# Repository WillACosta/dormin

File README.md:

## Dormin Split Keyboard

> 3×6 (+2 outer-pinky) Split Keyboard · 3 Thumb Keys · All 1U · MX Compatible

Dormin is a 42 — 36 keys split keyboard, inspired by some awesome keyboards that I've used and loved. The main goal is to create a customizable keyboard with optional features, but still as minimal as possible regarding the design.

### Must have specs

- Wireless Ble.
- Ultra low-profile build (<= 7mm).
- Low-profile switches and keycaps.
- Compatible with MX-Standard and the Gateron KS33/3.0 Low-Profile switches & Choc V2.
- Huge battery life (1200mAh).
- Minimalist and industrial design.
- Aluminum case and plate.
- 4 different layouts trough breakaway parts.
- Split and "Unibody" layouts (Using Pogo pins)
- MX-Spacing
- Status LEDs

**Optional**

- EC12 Rotatory Encoder
- SD OLED screen or Nice!View

## Layout Overview

The Dormin is a **40-key split keyboard** (20 keys per half) with a column-staggered matrix and a splayed thumb cluster.

| Zone | Columns | Rows | Keys/half | Notes |
|------|---------|------|-----------|-------|
| Matrix | 6 (outer → inner) | 3 (bottom, home, top) | 17 | Outer column skips bottom row (2 keys only) |
| Thumb | 3 (inner, home, outer) | 1 | 3 | Splayed arc, anchored below index |
| **Total** | | | **20** | **40 keys full board** |

### Column Stagger Profile

```
         outer  pinky  ring   middle  index  inner
stagger:   —    +u/2   +u/4   +u/4   −u/4   −u/4
mm:        0    +9.525 +4.763 +4.763 −4.763 −4.763
```

```
                    ┌──┐┌──┐
               ┌──┐ │  ││  │ ┌──┐
          ┌──┐ │  │ │Mi││Mi│ │  │ ┌──┐
     ┌──┐ │  │ │Ri││dd││dd│ │In│ │  │
     │  │ │Pi│ │ng││le││le│ │ne│ │  │
     │Ou│ │nk│ │  ││  ││  │ │r │ │  │
     │te│ │y │ │  ││  ││  │ │  │ │  │
     │r │ │  │ │  ││  ││  │ │  │ │  │
     └──┘ │  │ │  │└──┘└──┘ │  │ │  │
          └──┘ └──┘          └──┘ └──┘
                    ┌──┐
               ┌──┐│  │┌──┐
               │Th ││Th││Th│
               │ 3 ││ 2││ 1│
               └──┘└──┘└──┘
```

### Thumb Cluster Geometry

| Key | Splay | Spread | Stagger | Effective rotation |
|-----|-------|--------|---------|--------------------|
| thumb_inner | 0° | u (19.05mm) | 0mm | 0° |
| thumb_home | −15° | u+2.5 (21.55mm) | −2.7mm | −15° |
| thumb_outer | −14° | u+2.5 (21.55mm) | −2.5mm | −29° |

The thumb cluster anchors at `matrix_index_bottom` with a `[-0.1u, -1.30u]` offset, placing it slightly left and well below the index column — a natural resting position for the thumb.

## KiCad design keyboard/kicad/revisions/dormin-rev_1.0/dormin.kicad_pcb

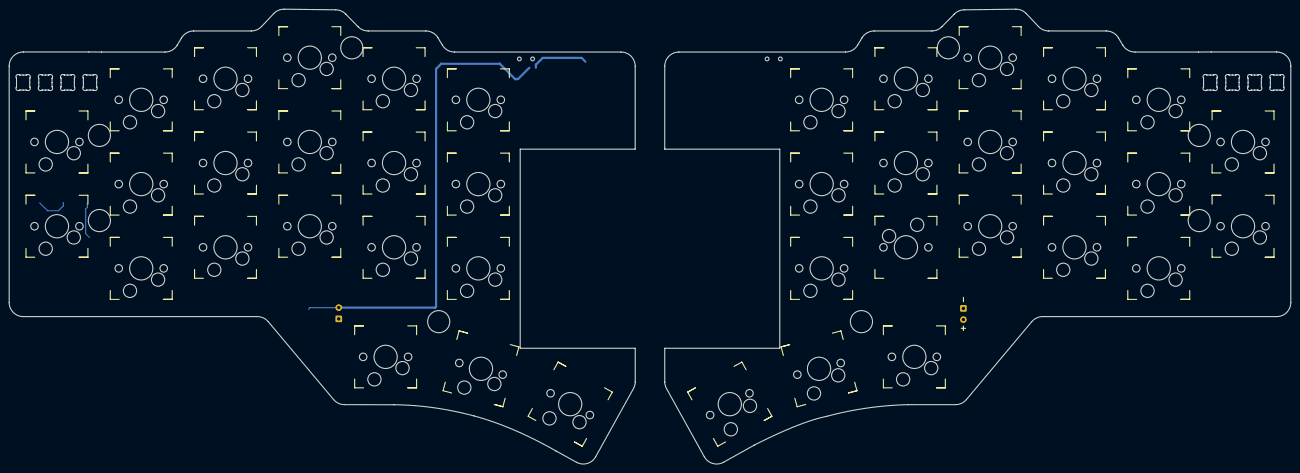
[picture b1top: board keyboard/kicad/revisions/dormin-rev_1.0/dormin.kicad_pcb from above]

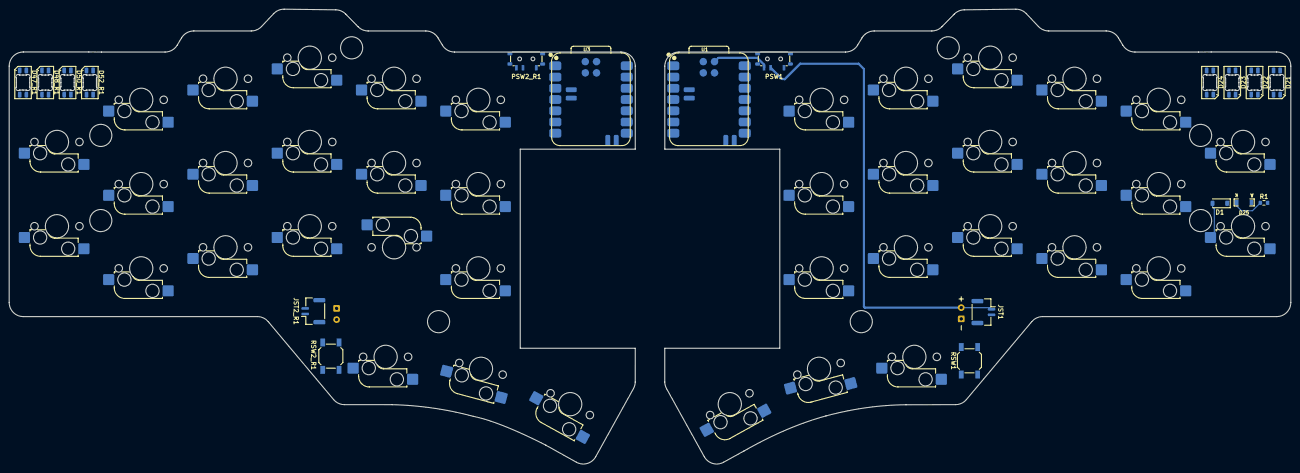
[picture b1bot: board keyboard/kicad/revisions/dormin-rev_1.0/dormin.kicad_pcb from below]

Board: 2 copper layers, 289.7 x 102.8 mm, 61 parts (20 on the bottom side), 31 nets.

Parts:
BT1, BT2_R1: Pads; Battery_Pad
D1: 1N4148W; D_SOD-123
D21, D22, D23, D24, D47_R1, D48_R1, D50_R1, D52_R1: SK6812MINI-E; LED_SK6812MINI-E_3.2x2.8mm_P1.5mm_ReverseMount
D25: LED; LED_MHT151WDT
JST1, JST2_R1: Conn_01x02_Pin; JST_GH_SM02B-GHS-TB_1x02-1MP_P1.25mm_Horizontal
PSW1, PSW2_R1: SW_SPDT; SW_MSK12C02-HB
R1: 1K; R_0603_1608Metric
RSW1, RSW2_R1: RSW1; SW_SPST_SKQG_WithStem
SW1, SW2, SW3, SW4, SW5, SW6, SW7, SW8, SW9, SW10, SW11, SW12, SW13, SW14, SW15, SW16, SW17, SW18, SW19, SW20, SW21, SW22, SW23, SW24, SW25, SW26, SW27, SW28, SW29, SW30, SW31, SW32, SW33, SW34, SW35, SW36, SW37, SW38, SW39, SW40: SW_Push; NF_LED_1206_SW_KS33_3_0_HS_1U
U1, U3: XIAO-nRF52840-SMD

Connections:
COL0: SW1.2, SW2.2, U3.5 (D4)
COL0_R: SW35.2, SW36.2, SW37.2, SW38.2, U1.5 (D4)
COL1: SW3.2, SW4.2, SW5.2, U3.6 (D5)
COL1_R: SW32.2, SW33.2, SW34.2, SW39.2, U1.6 (D5)
COL2: SW6.2, SW7.2, SW8.2, U3.7 (D6)
COL2_R: SW29.2, SW30.2, SW31.2, SW40.2, U1.7 (D6)
COL3: SW9.2, SW10.2, SW11.2, SW18.2, U3.8 (D7)
COL3_R: SW26.2, SW27.2, SW28.2, U1.8 (D7)
COL4: SW12.2, SW13.2, SW14.2, SW19.2, U3.9 (D8)
COL4_R: SW23.2, SW24.2, SW25.2, U1.9 (D8)
COL5: SW15.2, SW16.2, SW17.2, SW20.2, U3.10 (D9)
COL5_R: SW21.2, SW22.2, U1.10 (D9)
GND: BT1.2 (-), D21.1 (VSS), D22.1 (VSS), D23.1 (VSS), D24.1 (VSS), JST1.2, RSW1.2, U3.13 (GND), U3.18 (GND), U3.20 (GND)
GND_R: BT2_R1.2 (-), D47_R1.1 (VSS), D48_R1.1 (VSS), D50_R1.1 (VSS), D52_R1.1 (VSS), JST2_R1.2, RSW2_R1.2, U1.13 (GND), U1.18 (GND), U1.20 (GND)
unnamed: D1.2 (A), SW1.1
unnamed: D21.4 (DOUT), D22.2 (DIN)
unnamed: D21.3 (VDD), D22.3 (VDD), D23.3 (VDD), D24.3 (VDD)
unnamed: D22.4 (DOUT), D23.2 (DIN)
unnamed: D23.4 (DOUT), D24.2 (DIN)
unnamed: D25.1 (K), R1.1
unnamed: D47_R1.4 (DOUT), D48_R1.2 (DIN)
unnamed: D47_R1.3 (VDD), D48_R1.3 (VDD), D50_R1.3 (VDD), D52_R1.3 (VDD)
unnamed: D48_R1.4 (DOUT), D50_R1.2 (DIN)
unnamed: D50_R1.4 (DOUT), D52_R1.2 (DIN)
RESET: RSW1.1, U3.17 (EN)
RESET_R: RSW2_R1.1, U1.17 (EN)
ROW2: D1.1 (K), U3.3 (D2)
VBAT: D25.2 (A), PSW1.3 (C), U3.19 (VBAT)
VBAT_R: PSW2_R1.3 (C), U1.19 (VBAT)
VBAT_RAW: BT1.1 (+), JST1.1, PSW1.2 (B)
VBAT_RAW_R: BT2_R1.1 (+), JST2_R1.1, PSW2_R1.2 (B)

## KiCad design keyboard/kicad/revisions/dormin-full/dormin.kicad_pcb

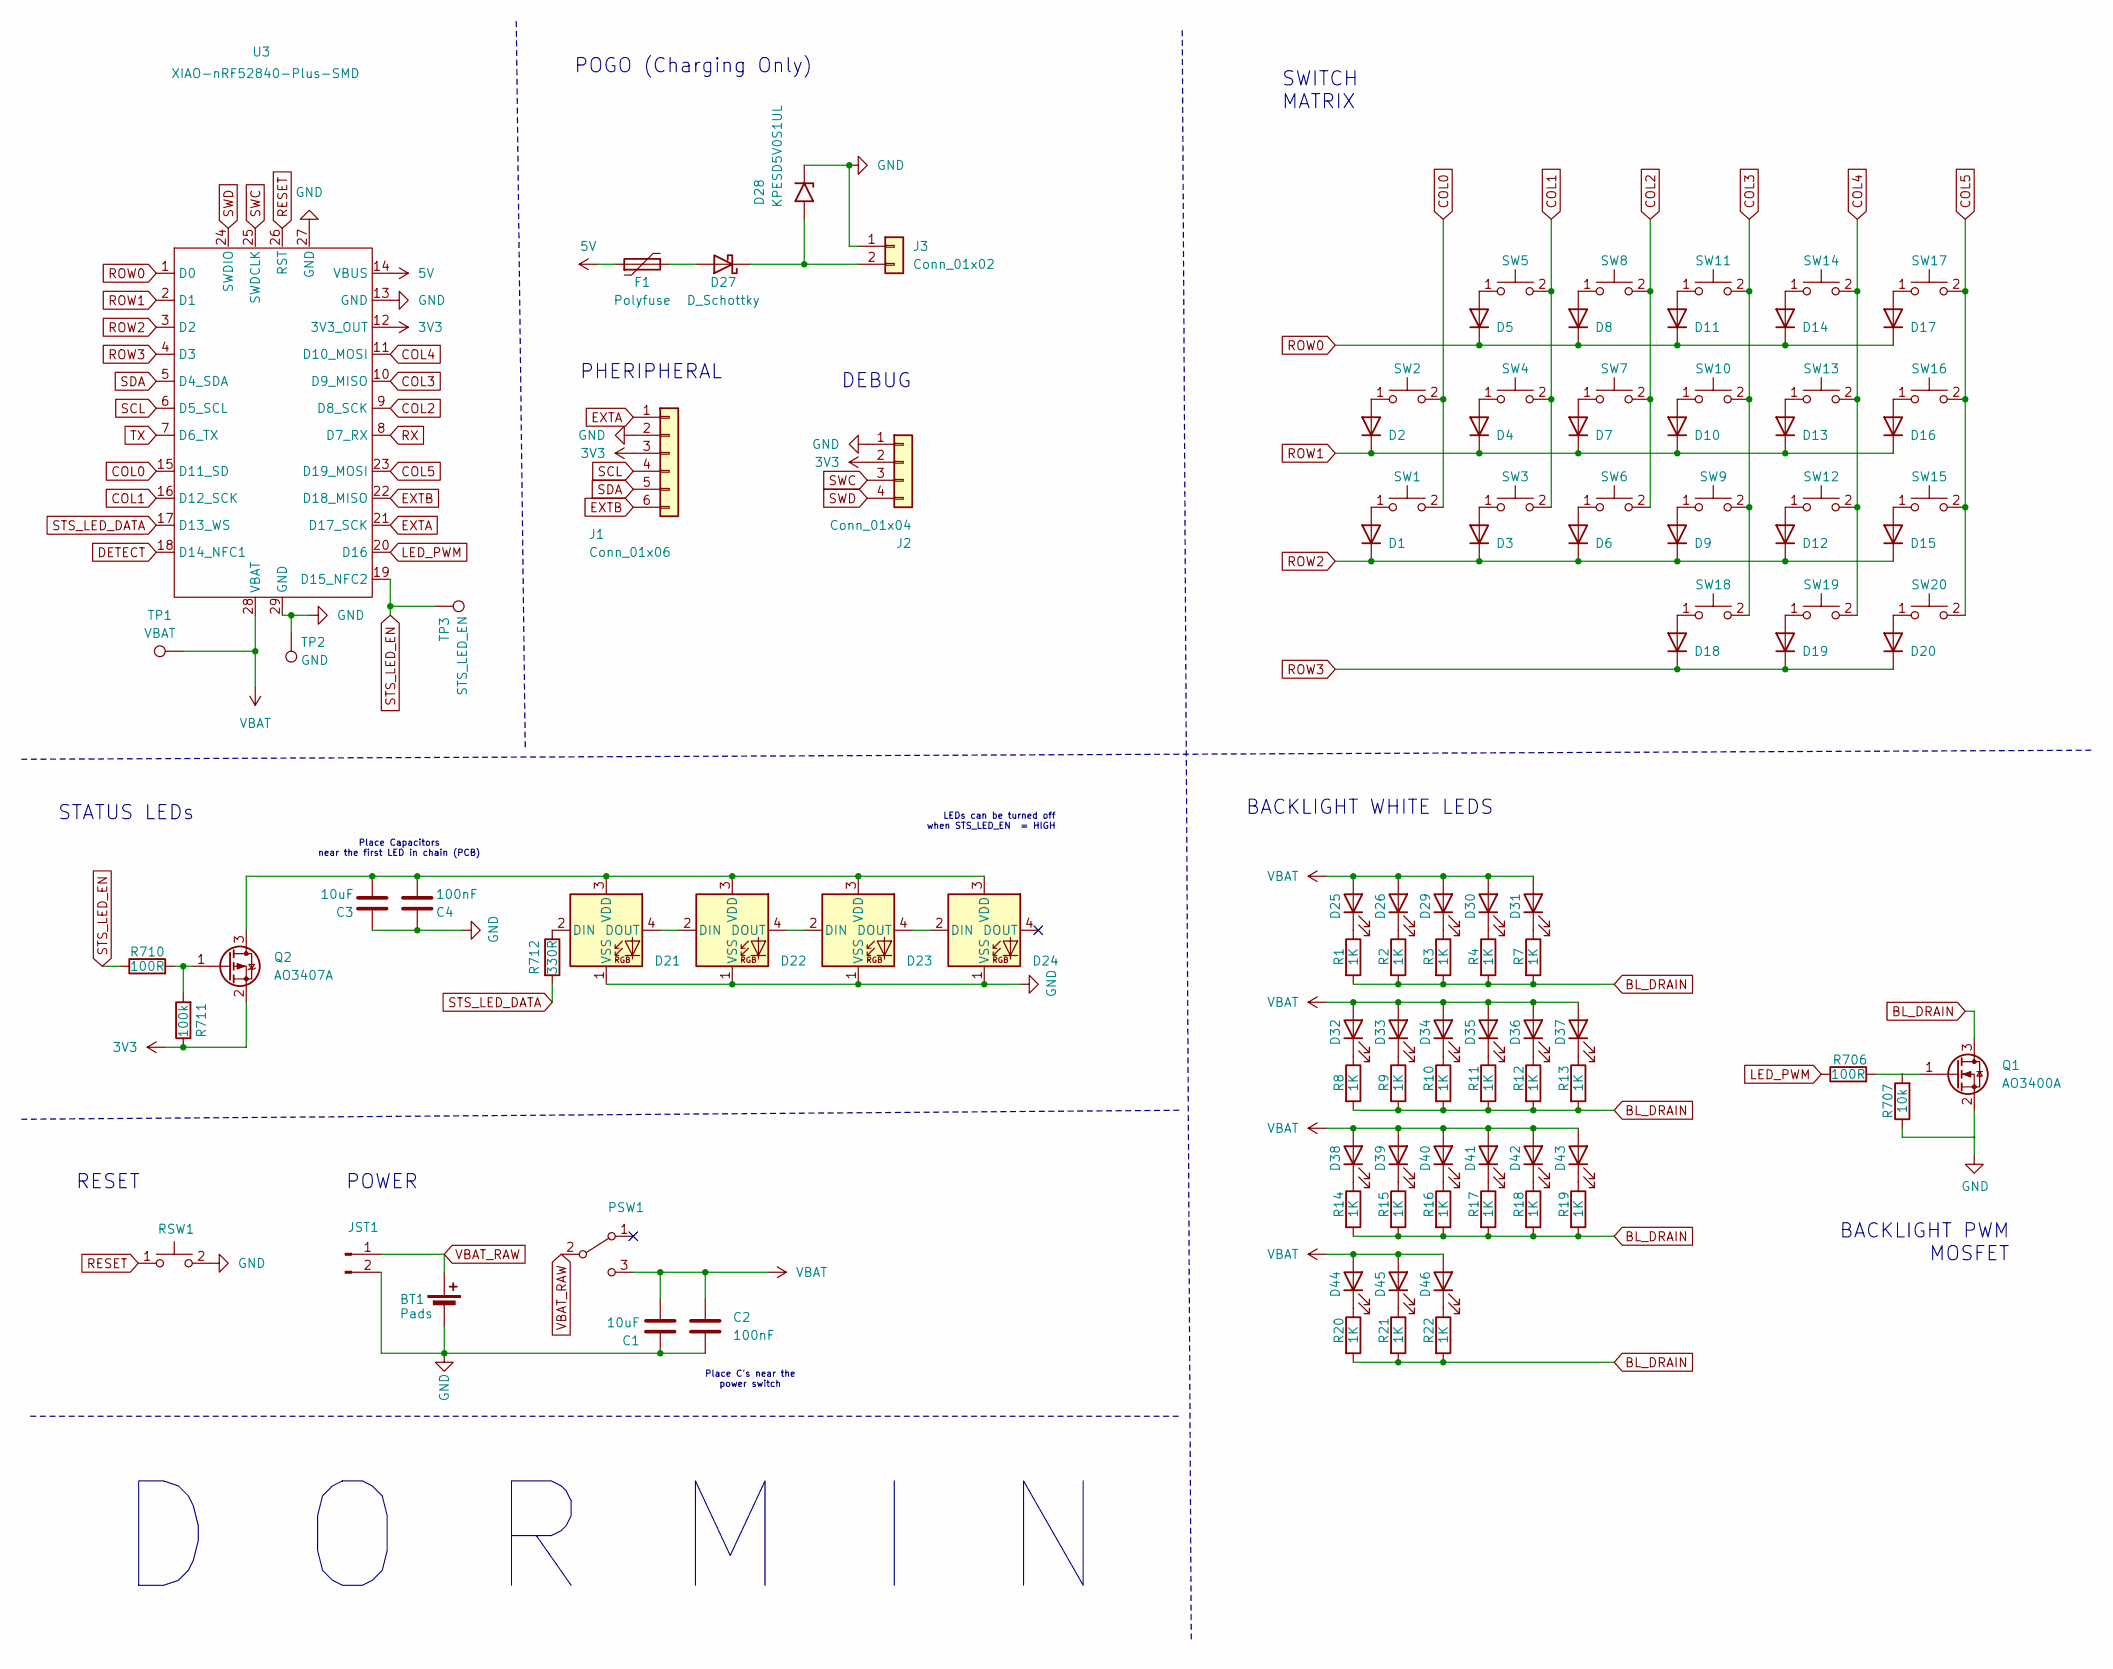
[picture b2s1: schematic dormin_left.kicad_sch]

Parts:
BT1: Pads; Battery_Pad
C1, C3: 10uF; C_0603_1608Metric
C2, C4: 100nF; C_0603_1608Metric
D1, D2, D3, D4, D5, D6, D7, D8, D9, D10, D11, D12, D13, D14, D15, D16, D17, D18, D19, D20: 1N4148W; D_SOD-123
D21, D22, D23, D24: SK6812MINI-E; LED_SK6812MINI-E_3.2x2.8mm_P1.5mm_ReverseMount
D25, D26, D29, D30, D31, D32, D33, D34, D35, D36, D37, D38, D39, D40, D41, D42, D43, D44, D45, D46: LED; LED_MHT151WDT
D27: D_Schottky; D_SOD-523
D28: KPESD5V0S1UL; D_SOD-882
F1: Polyfuse; Fuse_1206_3216Metric
J1: Conn_01x06; SMD_Conn_1x06_P2.54mm_Vertical
J2: Conn_01x04; PinSocket_1x04_P2.54mm_Vertical
J3: Conn_01x02; Pogo1x2-Right-Angle
JST1: Conn_01x02_Pin; JST_GH_SM02B-GHS-TB_1x02-1MP_P1.25mm_Horizontal
PSW1: SW_SPDT; SW_MSK12C02-HB
Q1: AO3400A; SOT-23
Q2: AO3407A; SOT-23; MPN AO3407A
R1, R2, R3, R4, R7, R8, R9, R10, R11, R12, R13, R14, R15, R16, R17, R18, R19, R20, R21, R22: 1K; R_0603_1608Metric
R706, R710: 100R; R_0603_1608Metric
R707: 10k; R_0603_1608Metric
R711: 100k; R_0603_1608Metric
R712: 330R; R_0603_1608Metric
RSW1: RSW1; SW_SPST_SKQG_WithStem
SW1, SW2, SW3, SW4, SW5, SW6, SW7, SW8, SW9, SW10, SW11, SW12, SW13, SW14, SW15, SW16, SW17, SW18, SW19, SW20: SW_Push; NF_LED_1206_SW_KS33_3_0_HS_1U
TP1: VBAT; TestPoint_Pad_D1.0mm
TP2: GND; TestPoint_Pad_D1.0mm
TP3: STS_LED_EN; TestPoint_Pad_D1.0mm
U3: XIAO-nRF52840-Plus-SMD

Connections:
3V3: J1.3, J2.2, Q2.2 (S), R711.1, U3.12 (3V3_OUT)
5V: F1.1, U3.14 (VBUS)
BL_DRAIN: Q1.3 (D), R1.2, R2.2, R3.2, R4.2, R7.2, R8.2, R9.2, R10.2, R11.2, R12.2, R13.2, R14.2, R15.2, R16.2, R17.2, R18.2, R19.2, R20.2, R21.2, R22.2
COL0: SW1.2, SW2.2, U3.15 (D11_SD)
COL1: SW3.2, SW4.2, SW5.2, U3.16 (D12_SCK)
COL2: SW6.2, SW7.2, SW8.2, U3.9 (D8_SCK)
COL3: SW9.2, SW10.2, SW11.2, SW18.2, U3.10 (D9_MISO)
COL4: SW12.2, SW13.2, SW14.2, SW19.2, U3.11 (D10_MOSI)
COL5: SW15.2, SW16.2, SW17.2, SW20.2, U3.23 (D19_MOSI)
DETECT: U3.18 (D14_NFC1)
EXTA: J1.1, U3.21 (D17_SCK)
EXTB: J1.6, U3.22 (D18_MISO)
GND: BT1.2 (-), C1.2, C2.2, C3.1, C4.2, D21.1 (VSS), D22.1 (VSS), D23.1 (VSS), D24.1 (VSS), D28.1 (A1), J1.2, J2.1, J3.1, JST1.2, Q1.2 (S), R707.1, RSW1.2, TP2.1 (1_1), U3.13 (GND), U3.27 (GND), U3.29 (GND)
LED_PWM: R706.1, U3.20 (D16)
unnamed: D1.2 (A), SW1.1
unnamed: D2.2 (A), SW2.1
unnamed: D3.2 (A), SW3.1
unnamed: D4.2 (A), SW4.1
unnamed: D5.2 (A), SW5.1
unnamed: D6.2 (A), SW6.1
unnamed: D7.2 (A), SW7.1
unnamed: D8.2 (A), SW8.1
unnamed: D9.2 (A), SW9.1
unnamed: D10.2 (A), SW10.1
unnamed: D11.2 (A), SW11.1
unnamed: D12.2 (A), SW12.1
unnamed: D13.2 (A), SW13.1
unnamed: D14.2 (A), SW14.1
unnamed: D15.2 (A), SW15.1
unnamed: D16.2 (A), SW16.1
unnamed: D17.2 (A), SW17.1
unnamed: D18.2 (A), SW18.1
unnamed: D19.2 (A), SW19.1
unnamed: D20.2 (A), SW20.1
unnamed: D21.2 (DIN), R712.1
unnamed: D21.4 (DOUT), D22.2 (DIN)
unnamed: C3.2, C4.1, D21.3 (VDD), D22.3 (VDD), D23.3 (VDD), D24.3 (VDD), Q2.3 (D)
unnamed: D22.4 (DOUT), D23.2 (DIN)
unnamed: D23.4 (DOUT), D24.2 (DIN)
unnamed: D25.1 (K), R1.1
unnamed: D26.1 (K), R2.1
unnamed: D27.2 (A), F1.2
unnamed: D27.1 (K), D28.2 (A2), J3.2
unnamed: D29.1 (K), R3.1
unnamed: D30.1 (K), R4.1
unnamed: D31.1 (K), R7.1
unnamed: D32.1 (K), R8.1
unnamed: D33.1 (K), R9.1
unnamed: D34.1 (K), R10.1
unnamed: D35.1 (K), R11.1
unnamed: D36.1 (K), R12.1
unnamed: D37.1 (K), R13.1
unnamed: D38.1 (K), R14.1
unnamed: D39.1 (K), R15.1
unnamed: D40.1 (K), R16.1
unnamed: D41.1 (K), R17.1
unnamed: D42.1 (K), R18.1
unnamed: D43.1 (K), R19.1
unnamed: D44.1 (K), R20.1
unnamed: D45.1 (K), R21.1
unnamed: D46.1 (K), R22.1
unnamed: Q1.1 (G), R706.2, R707.2
unnamed: Q2.1 (G), R710.2, R711.2
RESET: RSW1.1, U3.26 (RST)
ROW0: D5.1 (K), D8.1 (K), D11.1 (K), D14.1 (K), D17.1 (K), U3.1 (D0)
ROW1: D2.1 (K), D4.1 (K), D7.1 (K), D10.1 (K), D13.1 (K), D16.1 (K), U3.2 (D1)
ROW2: D1.1 (K), D3.1 (K), D6.1 (K), D9.1 (K), D12.1 (K), D15.1 (K), U3.3 (D2)
ROW3: D18.1 (K), D19.1 (K), D20.1 (K), U3.4 (D3)
RX: U3.8 (D7_RX)
SCL: J1.4, U3.6 (D5_SCL)
SDA: J1.5, U3.5 (D4_SDA)
STS_LED_DATA: R712.2, U3.17 (D13_WS)
STS_LED_EN: R710.1, TP3.1 (1_1), U3.19 (D15_NFC2)
SWC: J2.3, U3.25 (SWDCLK)
SWD: J2.4, U3.24 (SWDIO)
TX: U3.7 (D6_TX)
VBAT: C1.1, C2.1, D25.2 (A), D26.2 (A), D29.2 (A), D30.2 (A), D31.2 (A), D32.2 (A), D33.2 (A), D34.2 (A), D35.2 (A), D36.2 (A), D37.2 (A), D38.2 (A), D39.2 (A), D40.2 (A), D41.2 (A), D42.2 (A), D43.2 (A), D44.2 (A), D45.2 (A), D46.2 (A), PSW1.3 (C), TP1.1 (1_1), U3.28 (VBAT)
VBAT_RAW: BT1.1 (+), JST1.1, PSW1.2 (B)

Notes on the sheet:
DEBUG
LEDs can be turned off when STS_LED_EN = HIGH
RESET
Place C's near the power switch
Place Capacitors near the first LED in chain (PCB)
BACKLIGHT PWM MOSFET
POWER
D O R M I N
STATUS LEDs
BACKLIGHT WHITE LEDS
SWITCH MATRIX
PHERIPHERAL
POGO (Charging Only)

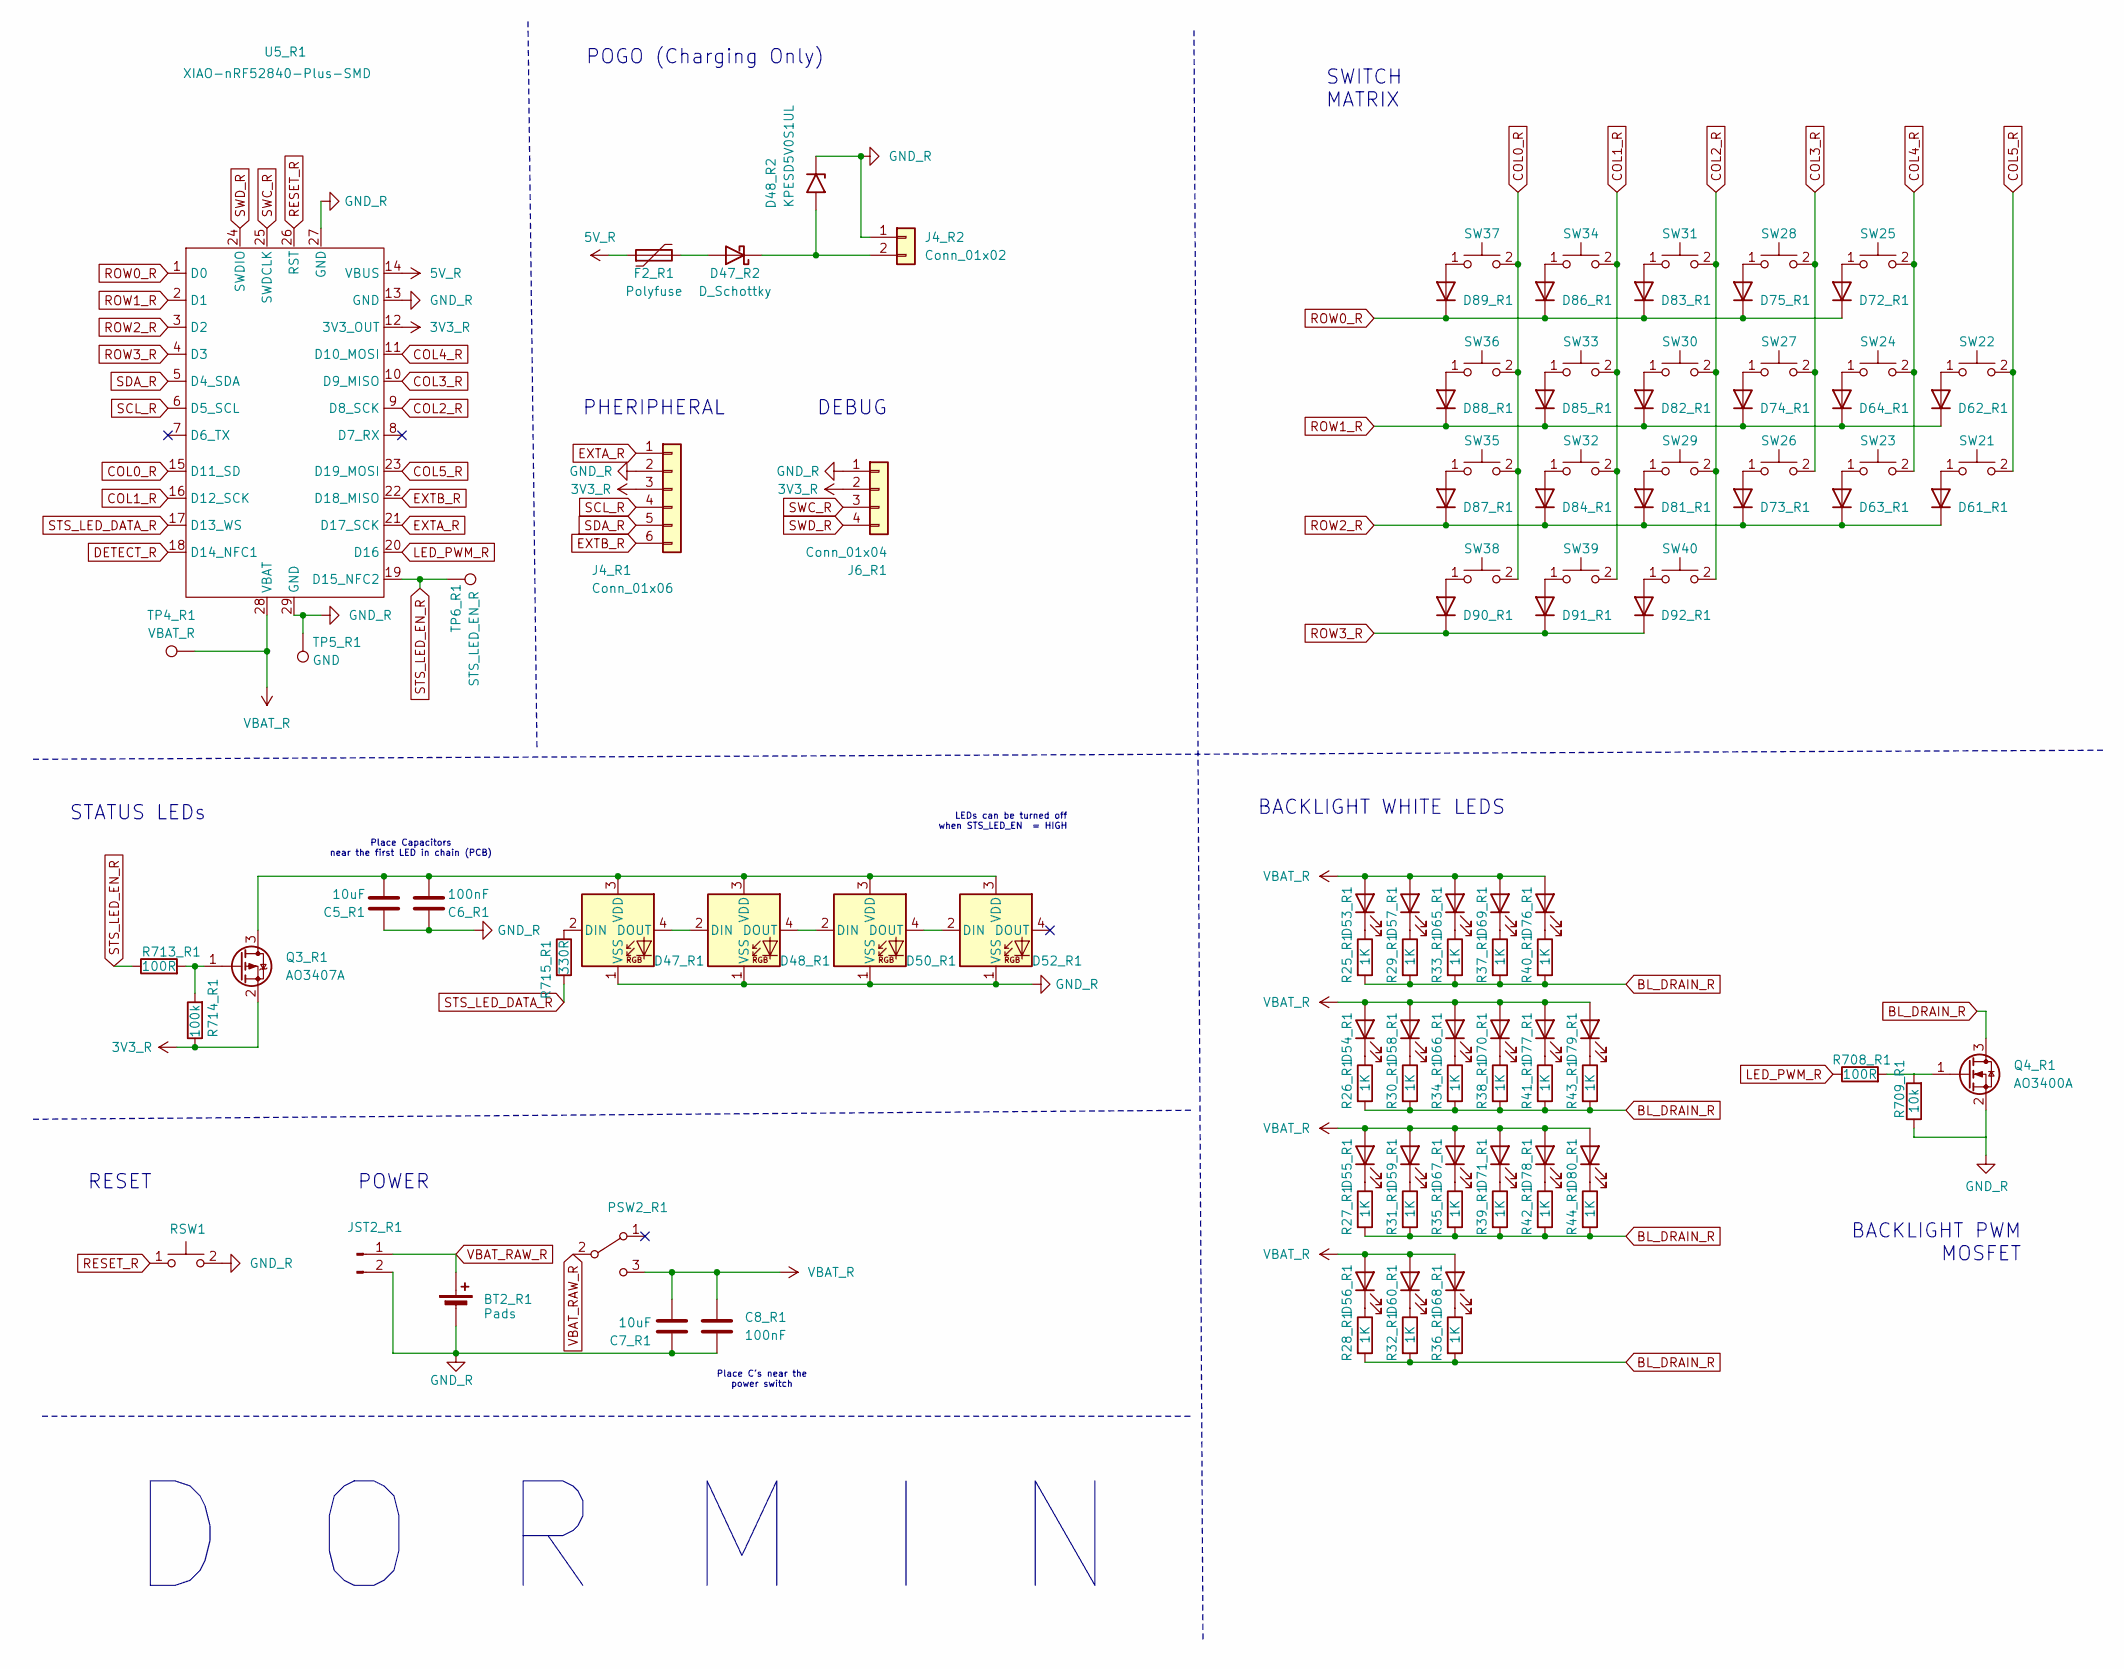
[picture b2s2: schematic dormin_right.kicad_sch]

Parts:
3V3_R01, 3V3_R02, 3V3_R03, 3V3_R04: 3V3_R
5V_R02: 5V_R
BT2_R1: Pads; Battery_Pad
C5_R1, C7_R1: 10uF; C_0603_1608Metric
C6_R1, C8_R1: 100nF; C_0603_1608Metric
D47_R1, D48_R1, D50_R1, D52_R1: SK6812MINI-E; LED_SK6812MINI-E_3.2x2.8mm_P1.5mm_ReverseMount
D47_R2: D_Schottky; D_SOD-523
D48_R2: KPESD5V0S1UL; D_SOD-882
D53_R1, D54_R1, D55_R1, D56_R1, D57_R1, D58_R1, D59_R1, D60_R1, D65_R1, D66_R1, D67_R1, D68_R1, D69_R1, D70_R1, D71_R1, D76_R1, D77_R1, D78_R1, D79_R1, D80_R1: LED; LED_MHT151WDT
D61_R1, D62_R1, D63_R1, D64_R1, D72_R1, D73_R1, D74_R1, D75_R1, D81_R1, D82_R1, D83_R1, D84_R1, D85_R1, D86_R1, D87_R1, D88_R1, D89_R1, D90_R1, D91_R1, D92_R1: 1N4148W; D_SOD-123
F2_R1: Polyfuse; Fuse_1206_3216Metric
GND_R03, GND_R04, GND_R05, GND_R06, GND_R07, GND_R08, GND_R09: GND_R
J4_R1: Conn_01x06; SMD_Conn_1x06_P2.54mm_Vertical
J4_R2: Conn_01x02; Pogo1x2-Right-Angle
J6_R1: Conn_01x04; PinSocket_1x04_P2.54mm_Vertical
JST2_R1: Conn_01x02_Pin; JST_GH_SM02B-GHS-TB_1x02-1MP_P1.25mm_Horizontal
PSW2_R1: SW_SPDT; SW_MSK12C02-HB
Q3_R1: AO3407A; SOT-23; MPN AO3407A
Q4_R1: AO3400A; SOT-23
R25_R1, R26_R1, R27_R1, R28_R1, R29_R1, R30_R1, R31_R1, R32_R1, R33_R1, R34_R1, R35_R1, R36_R1, R37_R1, R38_R1, R39_R1, R40_R1, R41_R1, R42_R1, R43_R1, R44_R1: 1K; R_0603_1608Metric
R708_R1, R713_R1: 100R; R_0603_1608Metric
R709_R1: 10k; R_0603_1608Metric
R714_R1: 100k; R_0603_1608Metric
R715_R1: 330R; R_0603_1608Metric
RSW2_R1: RSW1; SW_SPST_SKQG_WithStem
SW21, SW22, SW23, SW24, SW25, SW26, SW27, SW28, SW29, SW30, SW31, SW32, SW33, SW34, SW35, SW36, SW37, SW38, SW39, SW40: SW_Push; NF_LED_1206_SW_KS33_3_0_HS_1U
TP4_R1: VBAT_R; TestPoint_Pad_D1.0mm
TP5_R1: GND; TestPoint_Pad_D1.0mm
TP6_R1: STS_LED_EN_R; TestPoint_Pad_D1.0mm
U5_R1: XIAO-nRF52840-Plus-SMD
VBAT_R01: VBAT_R

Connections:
5V_R: 5V_R02.1, F2_R1.1, U5_R1.14 (VBUS)
BL_DRAIN_R: Q4_R1.3 (D), R25_R1.2, R26_R1.2, R27_R1.2, R28_R1.2, R29_R1.2, R30_R1.2, R31_R1.2, R32_R1.2, R33_R1.2, R34_R1.2, R35_R1.2, R36_R1.2, R37_R1.2, R38_R1.2, R39_R1.2, R40_R1.2, R41_R1.2, R42_R1.2, R43_R1.2, R44_R1.2
COL0_R: SW35.2, SW36.2, SW37.2, SW38.2, U5_R1.15 (D11_SD)
COL1_R: SW32.2, SW33.2, SW34.2, SW39.2, U5_R1.16 (D12_SCK)
COL2_R: SW29.2, SW30.2, SW31.2, SW40.2, U5_R1.9 (D8_SCK)
COL3_R: SW26.2, SW27.2, SW28.2, U5_R1.10 (D9_MISO)
COL4_R: SW23.2, SW24.2, SW25.2, U5_R1.11 (D10_MOSI)
COL5_R: SW21.2, SW22.2, U5_R1.23 (D19_MOSI)
DETECT_R: U5_R1.18 (D14_NFC1)
EXTA_R: J4_R1.1, U5_R1.21 (D17_SCK)
EXTB_R: J4_R1.6, U5_R1.22 (D18_MISO)
LED_PWM_R: R708_R1.1, U5_R1.20 (D16)
unnamed: D47_R1.2 (DIN), R715_R1.1
unnamed: D47_R1.4 (DOUT), D48_R1.2 (DIN)
unnamed: C5_R1.2, C6_R1.1, D47_R1.3 (VDD), D48_R1.3 (VDD), D50_R1.3 (VDD), D52_R1.3 (VDD), Q3_R1.3 (D)
unnamed: D47_R2.2 (A), F2_R1.2
unnamed: D47_R2.1 (K), D48_R2.2 (A2), J4_R2.2
unnamed: D48_R1.4 (DOUT), D50_R1.2 (DIN)
unnamed: D50_R1.4 (DOUT), D52_R1.2 (DIN)
unnamed: D53_R1.1 (K), R25_R1.1
unnamed: D54_R1.1 (K), R26_R1.1
unnamed: D55_R1.1 (K), R27_R1.1
unnamed: D56_R1.1 (K), R28_R1.1
unnamed: D57_R1.1 (K), R29_R1.1
unnamed: D58_R1.1 (K), R30_R1.1
unnamed: D59_R1.1 (K), R31_R1.1
unnamed: D60_R1.1 (K), R32_R1.1
unnamed: D61_R1.2 (A), SW21.1
unnamed: D62_R1.2 (A), SW22.1
unnamed: D63_R1.2 (A), SW23.1
unnamed: D64_R1.2 (A), SW24.1
unnamed: D65_R1.1 (K), R33_R1.1
unnamed: D66_R1.1 (K), R34_R1.1
unnamed: D67_R1.1 (K), R35_R1.1
unnamed: D68_R1.1 (K), R36_R1.1
unnamed: D69_R1.1 (K), R37_R1.1
unnamed: D70_R1.1 (K), R38_R1.1
unnamed: D71_R1.1 (K), R39_R1.1
unnamed: D72_R1.2 (A), SW25.1
unnamed: D73_R1.2 (A), SW26.1
unnamed: D74_R1.2 (A), SW27.1
unnamed: D75_R1.2 (A), SW28.1
unnamed: D76_R1.1 (K), R40_R1.1
unnamed: D77_R1.1 (K), R41_R1.1
unnamed: D78_R1.1 (K), R42_R1.1
unnamed: D79_R1.1 (K), R43_R1.1
unnamed: D80_R1.1 (K), R44_R1.1
unnamed: D81_R1.2 (A), SW29.1
unnamed: D82_R1.2 (A), SW30.1
unnamed: D83_R1.2 (A), SW31.1
unnamed: D84_R1.2 (A), SW32.1
unnamed: D85_R1.2 (A), SW33.1
unnamed: D86_R1.2 (A), SW34.1
unnamed: D87_R1.2 (A), SW35.1
unnamed: D88_R1.2 (A), SW36.1
unnamed: D89_R1.2 (A), SW37.1
unnamed: D90_R1.2 (A), SW38.1
unnamed: D91_R1.2 (A), SW39.1
unnamed: D92_R1.2 (A), SW40.1
unnamed: Q3_R1.1 (G), R713_R1.2, R714_R1.2
unnamed: Q4_R1.1 (G), R708_R1.2, R709_R1.2
RESET_R: RSW2_R1.1, U5_R1.26 (RST)
ROW0_R: D72_R1.1 (K), D75_R1.1 (K), D83_R1.1 (K), D86_R1.1 (K), D89_R1.1 (K), U5_R1.1 (D0)
ROW1_R: D62_R1.1 (K), D64_R1.1 (K), D74_R1.1 (K), D82_R1.1 (K), D85_R1.1 (K), D88_R1.1 (K), U5_R1.2 (D1)
ROW2_R: D61_R1.1 (K), D63_R1.1 (K), D73_R1.1 (K), D81_R1.1 (K), D84_R1.1 (K), D87_R1.1 (K), U5_R1.3 (D2)
ROW3_R: D90_R1.1 (K), D91_R1.1 (K), D92_R1.1 (K), U5_R1.4 (D3)
SCL_R: J4_R1.4, U5_R1.6 (D5_SCL)
SDA_R: J4_R1.5, U5_R1.5 (D4_SDA)
STS_LED_DATA_R: R715_R1.2, U5_R1.17 (D13_WS)
STS_LED_EN_R: R713_R1.1, TP6_R1.1 (1_1), U5_R1.19 (D15_NFC2)
SWC_R: J6_R1.3, U5_R1.25 (SWDCLK)
SWD_R: J6_R1.4, U5_R1.24 (SWDIO)
VBAT_RAW_R: BT2_R1.1 (+), JST2_R1.1, PSW2_R1.2 (B)

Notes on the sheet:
STATUS LEDs
SWITCH MATRIX
Place C's near the power switch
D O R M I N
RESET
BACKLIGHT PWM MOSFET
LEDs can be turned off when STS_LED_EN = HIGH
DEBUG
Place Capacitors near the first LED in chain (PCB)
BACKLIGHT WHITE LEDS
PHERIPHERAL
POGO (Charging Only)
POWER

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
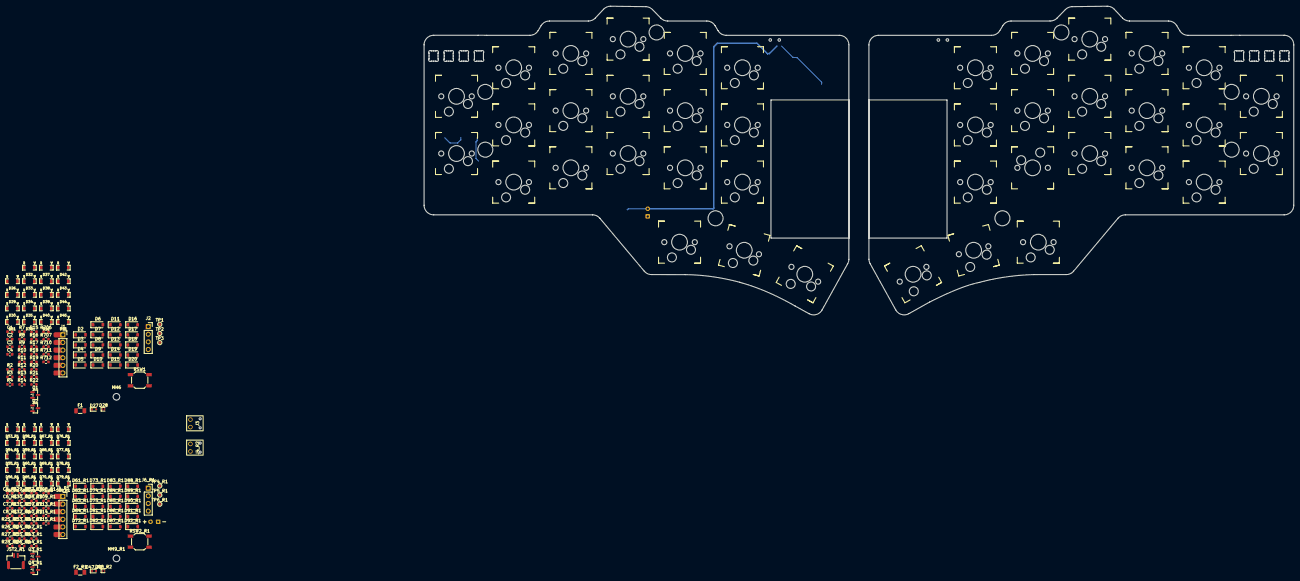
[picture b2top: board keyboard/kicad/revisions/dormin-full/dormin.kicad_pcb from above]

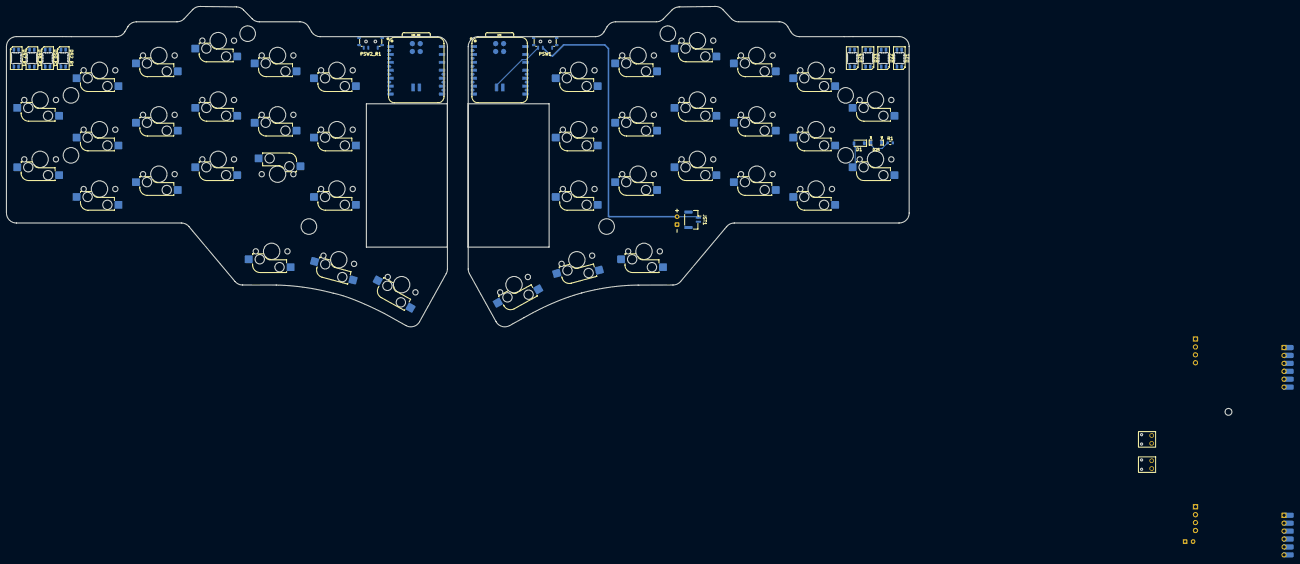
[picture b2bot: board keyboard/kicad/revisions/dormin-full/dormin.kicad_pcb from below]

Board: 2 copper layers, 220 parts (17 on the bottom side), 150 nets.

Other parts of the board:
MH6, MH9_R1: MountingHole_2.2mm_M2

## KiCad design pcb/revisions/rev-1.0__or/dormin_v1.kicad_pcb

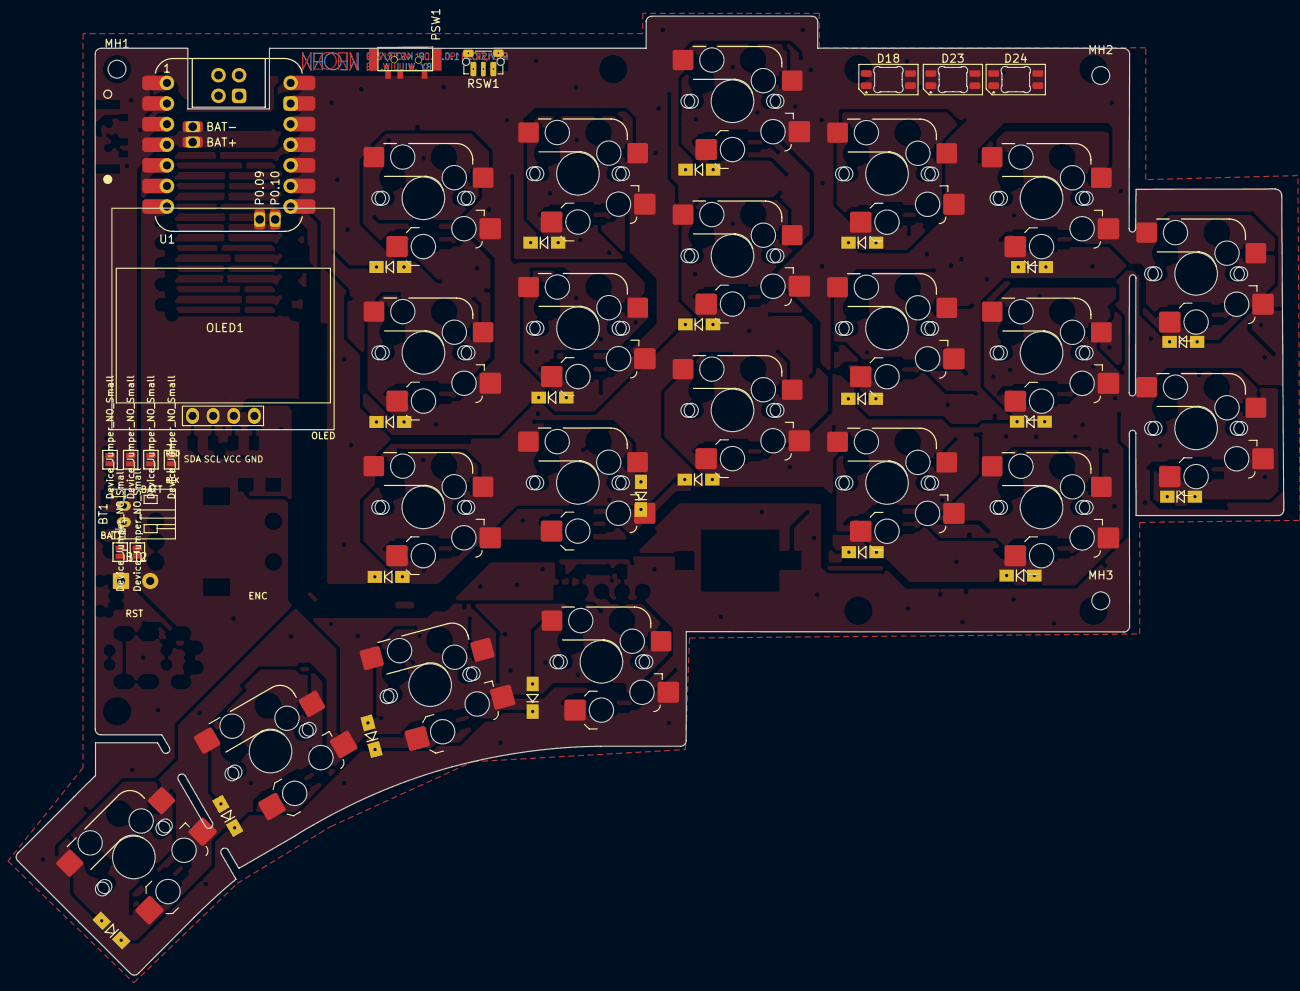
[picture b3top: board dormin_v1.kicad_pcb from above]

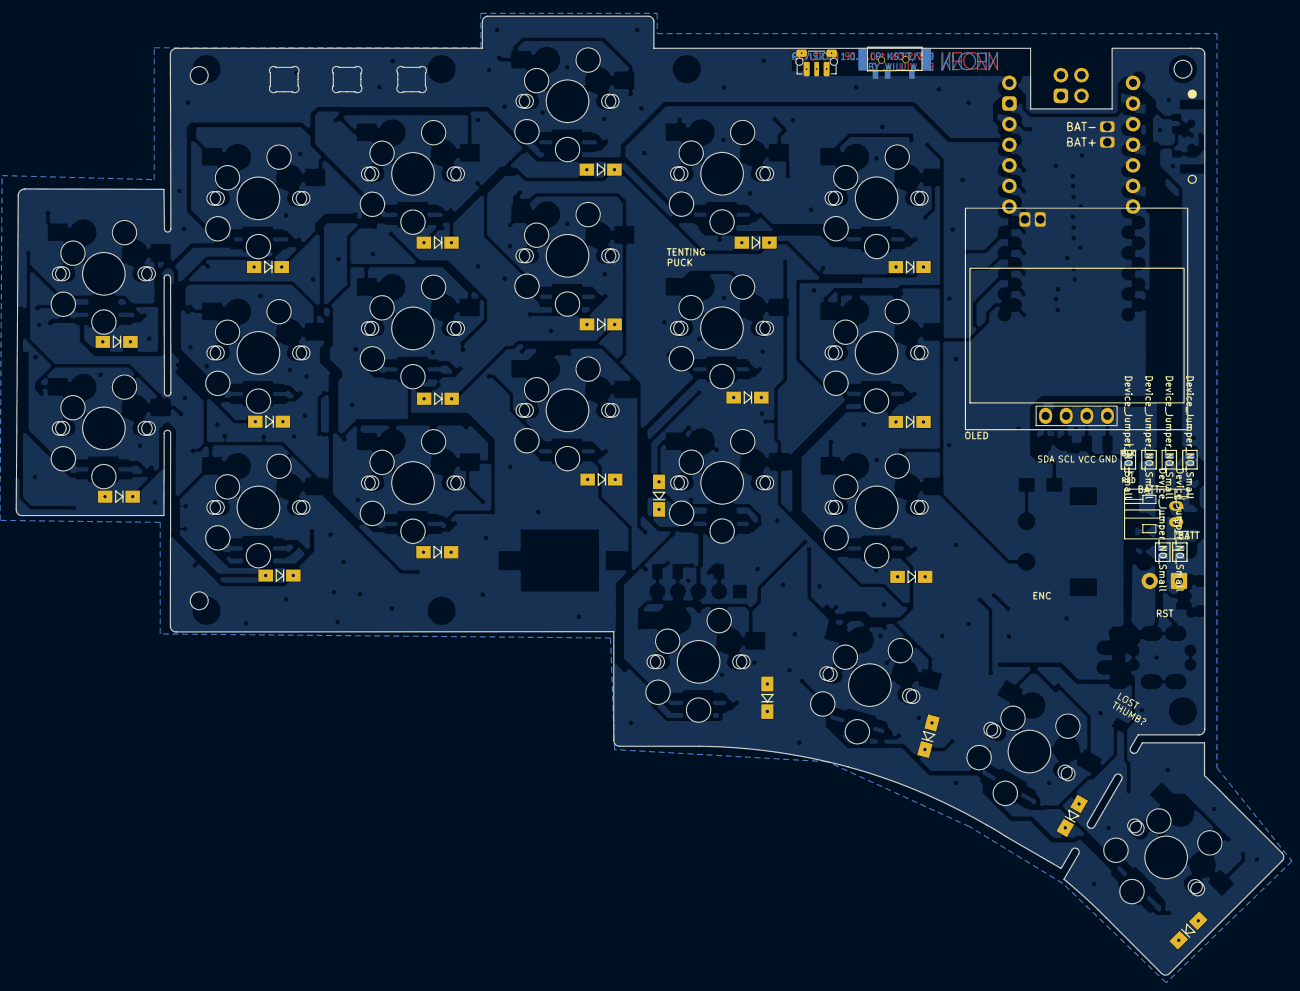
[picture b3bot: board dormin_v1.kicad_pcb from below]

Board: 2 copper layers, 156.2 x 118.2 mm, 68 parts (6 on the bottom side), 19 nets, no tracks yet.

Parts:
BT1: JST Connector; JST_PH_reversible
BT2: Battery_Cell; custombatteryconnector_small
D1, D2, D3, D4, D5, D6, D7, D8, D9, D10, D11, D12, D13, D14, D15, D16, D17, D19, D20, D21, D22: D_Small; Diode_SOD123
D18, D23, D24: SK6812MINI-E; LED_SK6812MINI-E_3.2x2.8mm_P1.5mm_ReverseMount
JP1, JP2, JP3, JP4, JP5, JP6, JP7, JP8, JP22, JP23, JP24, JP25: Device_Jumper_NO_Small; Jumper
MH1, MH2, MH3, MH4, MH5: MountingHole_2.2mm_M2
OLED1: SSD1306; SSD1306_128x64OLED
PSW1: SW_DPDT_x2; MSK12C02_reversible
RSW1: SW_Push; SW_Push_1P1T-MP_NO_Horizontal_Alps_SKRTLAE010_both_sides
SW1, SW2, SW3, SW4, SW5, SW6, SW7, SW8, SW9, SW10, SW11, SW12, SW13, SW14, SW15, SW16, SW17, SW19, SW20, SW21, SW22: SW_PUSH-MX_CHOC; SW_MXchoc_HS_1u
U1: Seeeduino Xiao nRF52840; Xiao_nRF52840_ACH

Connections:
/BAT-: BT1.2 (-), JP24.1, JP25.1
/PSW: BT2.1 (+), JP23.2, JP24.2, PSW1.2 (B)
BAT+: BT1.1 (+), JP22.1, JP23.1, U1.16 (BAT+)
GND: BT2.2 (-), D18.1 (VSS), D23.1 (VSS), D24.1 (VSS), JP1.2, JP8.2, JP22.2, JP25.2, RSW1.1, U1.9 (GND), U1.15 (BAT-), U1.22 (GND)
LED: D18.2 (DIN), U1.11 (P1.15)
unnamed: D18.4 (DOUT), D23.2 (DIN)
unnamed: D23.4 (DOUT), D24.2 (DIN)
unnamed: JP1.1, JP5.1, OLED1.1 (GND)
unnamed: JP3.1, JP7.1, OLED1.3 (SCL)
unnamed: JP4.1, JP8.1, OLED1.4 (SDA)
unnamed: JP2.1, JP6.1, OLED1.2 (VCC)
RESET: RSW1.2, U1.21 (RST)
SCL: JP3.2, JP6.2, U1.6 (P0.05)
SDA: JP4.2, JP5.2, U1.5 (P0.04)
VCC: D18.3 (VDD), D23.3 (VDD), D24.3 (VDD), JP2.2, JP7.2, U1.10 (3V3)
row0: D1.1 (K), D2.1 (K), D3.1 (K), D4.1 (K), D5.1 (K), U1.1 (P0.02)
row1: D6.1 (K), D7.1 (K), D8.1 (K), D9.1 (K), D10.1 (K), D11.1 (K), U1.2 (P0.03)
row2: D12.1 (K), D13.1 (K), D14.1 (K), D15.1 (K), D16.1 (K), D17.1 (K), U1.3 (P0.28)
row3: D19.1 (K), D20.1 (K), D21.1 (K), D22.1 (K), U1.4 (P0.29)
